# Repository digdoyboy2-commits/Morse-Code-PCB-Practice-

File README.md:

# Morse-Code-PCB-Practice-
custom pcb design for a pocket-sized morse code trainer powered by a seeed studio xiao esp32-s3 microcontroller, featuring an i2c oled display, tactile buttons, and an onboard buzzer.

Pocket Morse Code Trainer

A custom-designed, pocket-sized Morse Code training device powered by a Seeed Studio XIAO ESP32-S3 microcontroller. 
It features a 0.96-inch I2C OLED display for real-time visual feedback, four tactile buttons for handling dits, dahs, enter, and reset functions, and an onboard buzzer for audio sidetone feedback.
The custom 2-layer PCB was engineered from scratch in KiCad with a full ground pour for signal integrity and an accessible USB-C port for power and firmware flashing.

Design & Layout

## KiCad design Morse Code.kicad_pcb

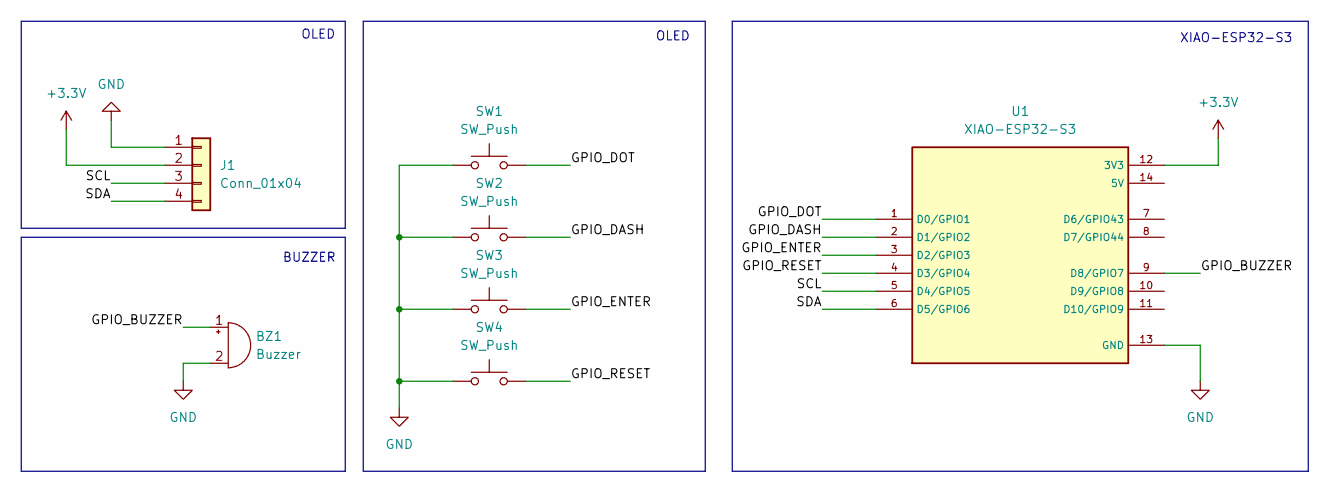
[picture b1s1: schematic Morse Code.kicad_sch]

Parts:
BZ1: Buzzer; Buzzer_12x9.5RM7.6
J1: Conn_01x04; Display_128x64_096_I2C
SW1, SW2, SW3, SW4: SW_Push; SW_PUSH_6mm
U1: XIAO-ESP32-S3; XIAO ESP32-S3; PARTREV April 22nd, 2026

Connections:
+3.3V: J1.2, U1.12 (3V3)
/GPIO_BUZZER: BZ1.1 (+), U1.9 (D8/GPIO7)
/GPIO_DASH: SW2.2, U1.2 (D1/GPIO2)
/GPIO_DOT: SW1.2, U1.1 (D0/GPIO1)
/GPIO_ENTER: SW3.2, U1.3 (D2/GPIO3)
/GPIO_RESET: SW4.2, U1.4 (D3/GPIO4)
/SCL: J1.3, U1.5 (D4/GPIO5)
/SDA: J1.4, U1.6 (D5/GPIO6)
GND: BZ1.2 (-), J1.1, SW1.1, SW2.1, SW3.1, SW4.1, U1.13 (GND)

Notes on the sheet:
XIAO-ESP32-S3
BUZZER
OLED

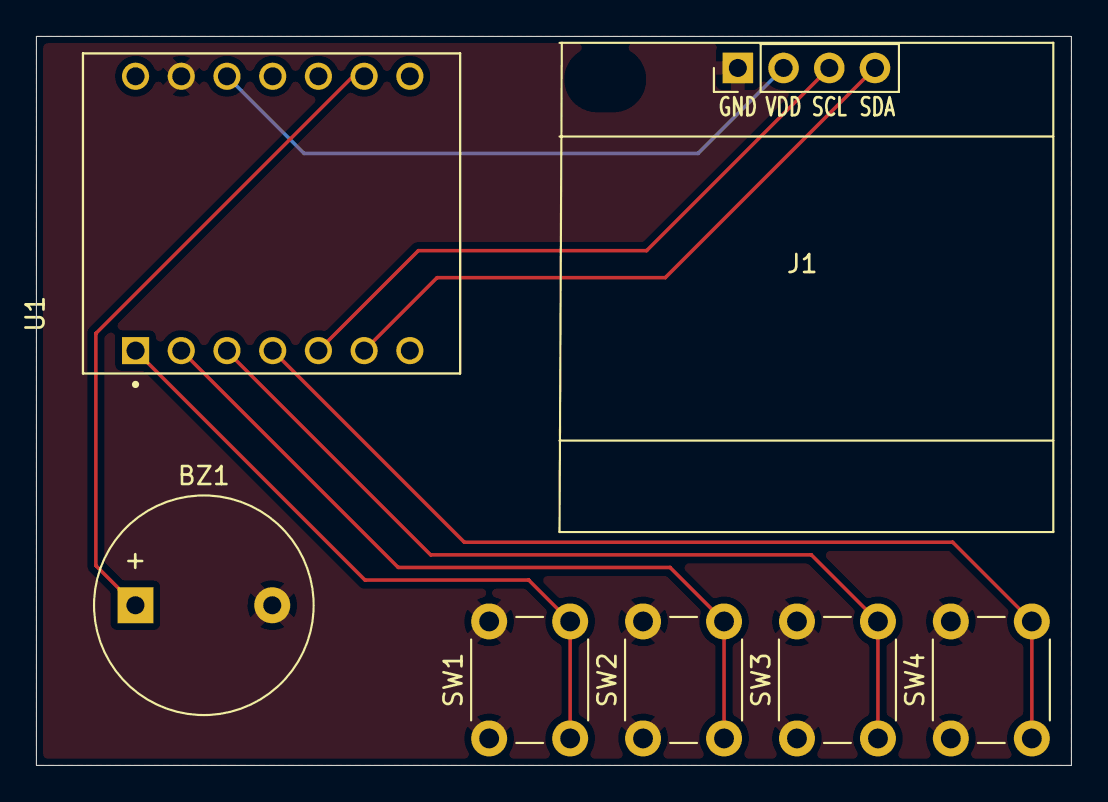
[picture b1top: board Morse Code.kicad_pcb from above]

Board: 2 copper layers, 57.5 x 40.5 mm, 7 parts (0 on the bottom side), 9 nets.
